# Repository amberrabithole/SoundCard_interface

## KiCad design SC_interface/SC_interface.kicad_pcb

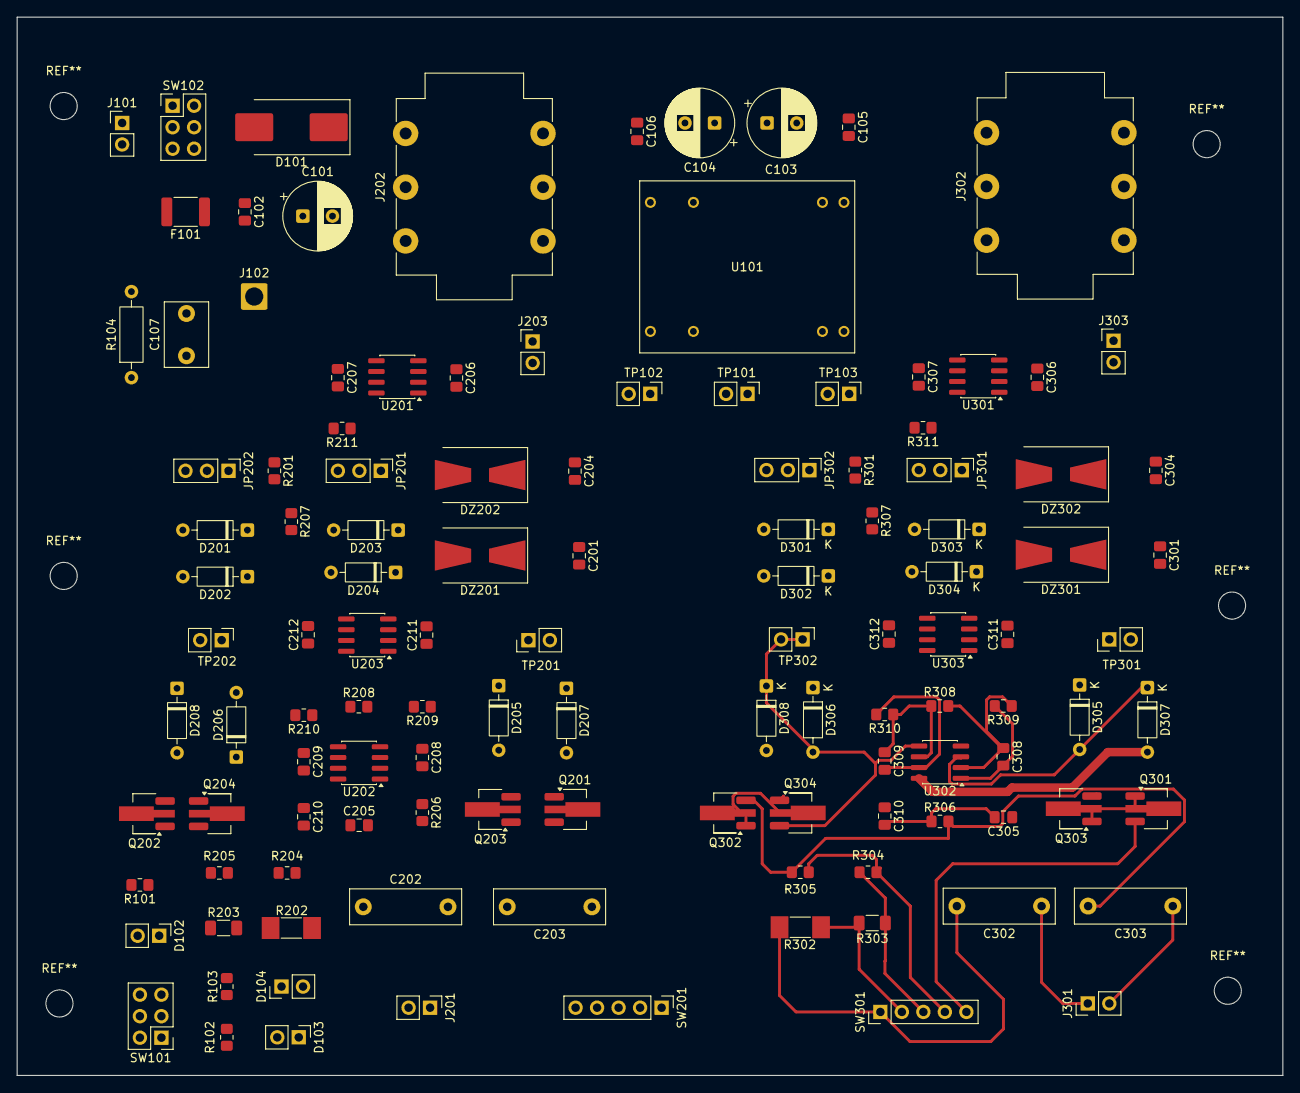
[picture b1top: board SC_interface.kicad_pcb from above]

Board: 2 copper layers, 149.5 x 125.0 mm, 120 parts (0 on the bottom side), 65 nets.

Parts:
C101, C103, C104: 330uf 25V; CP_Radial_D8.0mm_P3.50mm
C102, C105, C106, C201, C204, C205, C206, C207, C210, C211, C212, C301, C304, C305, C306, C307, C310, C311, C312: 0.1uf; C_0805_2012Metric_Pad1.18x1.45mm_HandSolder
C107: 10nF 1kV; C_Disc_D7.5mm_W5.0mm_P5.00mm
C202, C203, C302, C303: 0.47uf 400V; C_Rect_L13.0mm_W4.0mm_P10.00mm_FKS3_FKP3_MKS4
C208, C209, C308, C309: 15pF; C_0805_2012Metric_Pad1.18x1.45mm_HandSolder
D101: SMCJ6.0A; D_SMC_Handsoldering
D102: M_PWR; PinHeader_1x02_P2.54mm_Vertical
D103: PWR_PS; PinHeader_1x02_P2.54mm_Vertical
D104: PWR_NEG; PinHeader_1x02_P2.54mm_Vertical
D201, D202, D203, D204, D205, D206, D207, D208, D301, D302, D303, D304, D305, D306, D307, D308: 1N4148; D_DO-35_SOD27_P7.62mm_Horizontal
DZ201, DZ202, DZ301, DZ302: 1SMB5917; D_SMB-SMC_Universal_Handsoldering
F101: MF-MSMF110; Fuse_1812_4532Metric_Pad1.30x3.40mm_HandSolder
J101: 5V_PWR; PinHeader_1x02_P2.54mm_Vertical
J102: J_chassis; SolderWire-1.5sqmm_1x01_D1.7mm_OD3mm
J201, J301: Input; PinHeader_1x02_P2.54mm_Vertical
J202, J302: BalancedOut; Jack_6.35mm_Neutrik_NMJ6HCD2_Horizontal
J203, J303: Output_BNC; PinHeader_1x02_P2.54mm_Vertical
JP201, JP301: Clamp1; PinHeader_1x03_P2.54mm_Vertical
JP202, JP302: Clamp2; PinHeader_1x03_P2.54mm_Vertical
Q201, Q202, Q203, Q204, Q301, Q302, Q303, Q304: LND150N8; SOT-89-3_Handsoldering
R101: 470R; R_0805_2012Metric_Pad1.20x1.40mm_HandSolder
R102, R103: 3K; R_0805_2012Metric_Pad1.20x1.40mm_HandSolder
R104: 1M, 1W; R_Axial_DIN0207_L6.3mm_D2.5mm_P10.16mm_Horizontal
R201, R207, R301, R307: 1k; R_0805_2012Metric_Pad1.20x1.40mm_HandSolder
R202, R302: 90.9k; R_MELF_MMB-0207
R203, R303: 9.09k; R_1206_3216Metric_Pad1.30x1.75mm_HandSolder
R204, R304: 909; R_0805_2012Metric_Pad1.20x1.40mm_HandSolder
R205, R305: 102; R_0805_2012Metric_Pad1.20x1.40mm_HandSolder
R206, R306: 100k; R_0805_2012Metric_Pad1.20x1.40mm_HandSolder
R208, R308: 10k; R_0805_2012Metric_Pad1.20x1.40mm_HandSolder
R209, R210, R309, R310: 7.5k; R_0805_2012Metric_Pad1.20x1.40mm_HandSolder
R211, R311: 200R; R_0805_2012Metric_Pad1.20x1.40mm_HandSolder
SW101: Main Power; PinHeader_2x03_P2.54mm_Vertical
SW102: Master SW; PinHeader_2x03_P2.54mm_Vertical
SW201, SW301: SW_Select1; PinHeader_1x05_P2.54mm_Vertical
TP101: TP_POS; PinHeader_1x02_P2.54mm_Vertical
TP102: TP_NEG; PinHeader_1x02_P2.54mm_Vertical
TP103: TP_GND; PinHeader_1x02_P2.54mm_Vertical
TP201, TP301: TP_IN_HOT; PinHeader_1x02_P2.54mm_Vertical
TP202, TP302: TP_IN_COLD; PinHeader_1x02_P2.54mm_Vertical
U101: JCA0305D03; XPDCDCCONV
U201, U301: DRV135UA; SOIC-8_3.9x4.9mm_P1.27mm
U202, U302: U2 OPA1656IDR; SOIC-8_3.9x4.9mm_P1.27mm
U203, U303: INA134UA; SOIC-8_3.9x4.9mm_P1.27mm

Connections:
+VDC: C205.1, C207.1, C212.1, C305.1, C307.1, C312.1, D207.2 (A), D208.2 (A), D307.2 (A), D308.2 (A), R102.1, R201.2, R301.2, SW101.3 (C), TP101.1, TP101.2, U201.6 (V+), U202.8 (V+), U203.7 (V+), U301.6 (V+), U302.8 (V+), U303.7 (V+)
-VDC: C206.2, C210.1, C211.1, C306.2, C310.1, C311.1, D205.1 (K), D206.1 (K), D305.1 (K), D306.1 (K), R103.1, R207.1, R307.1, SW101.6 (C), TP102.1, TP102.2, U201.5 (V-), U202.4 (V-), U203.4 (V-), U301.5 (V-), U302.4 (V-), U303.4 (V-)
/5V_in: J101.1, SW102.2 (B), SW102.5 (B)
/GNDREF: C101.2, C102.2, D101.2 (A), D102.1 (K), J101.2, U101.2 (-VIN), U101.3 (-VIN2)
/Input_ChannelL/SCPROT: D201.1 (K), D203.2 (A), J203.1 (In), R211.2, U201.4 (VIN)
/Input_ChannelL/VOut_neg: J202.R, U201.1 (-VO), U201.2 (-SENSE)
/Input_ChannelL/VOut_pos: J202.T, U201.7 (+SENSE), U201.8 (+VO)
/Input_ChannelR/SCPROT: D301.1 (K), D303.2 (A), J303.1 (In), R311.2, U301.4 (VIN)
/Input_ChannelR/VOut_neg: J302.R, U301.1 (-VO), U301.2 (-SENSE)
/Input_ChannelR/VOut_pos: J302.T, U301.7 (+SENSE), U301.8 (+VO)
GND: C103.2, C104.1, C105.2, C106.2, C107.2, C201.1, C204.1, C205.2, C206.1, C207.2, C210.2, C211.2, C212.2, C301.1, C304.1, C305.2, C306.1, C307.2, C310.2, C311.2, C312.2, D103.1 (K), D104.2 (A), D202.2 (A), D204.1 (K), D302.2 (A), D304.1 (K), DZ201.2 (A), DZ202.1 (K), DZ301.2 (A), DZ302.1 (K), J202.S, J203.2 (Ext), J302.S, J303.2 (Ext), R104.2, R206.1, R306.1, TP103.1, TP103.2, U101.9 (COMMON), U101.16 (COMMON2), U201.3 (GND), U203.1 (REF), U301.3 (GND), U303.1 (REF)
unnamed: C202.2, R202.2, SW201.1
unnamed: C302.2, R302.2, SW301.1
unnamed: C101.1, C102.1, D101.1 (K), F101.2, R101.1, U101.22 (+VIN), U101.23 (+VIN2)
unnamed: D102.2 (A), R101.2
unnamed: D103.2 (A), R102.2
unnamed: D104.1 (K), R103.2
unnamed: D201.2 (A), JP201.2 (C), R201.1
unnamed: D202.1 (K), JP201.1 (A)
unnamed: D203.1 (K), JP202.2 (C), R207.2
unnamed: D204.2 (A), JP202.1 (A)
unnamed: D205.2 (A), D207.1 (K), Q203.3 (D), TP201.1, TP201.2, U202.3 (+)
unnamed: D206.2 (A), D208.1 (K), Q204.3 (D), TP202.1, TP202.2, U202.5 (+)
unnamed: D301.2 (A), JP301.2 (C), R301.1
unnamed: D302.1 (K), JP301.1 (A)
unnamed: D303.1 (K), JP302.2 (C), R307.2
unnamed: D304.2 (A), JP302.1 (A)
unnamed: D305.2 (A), D307.1 (K), Q303.3 (D), TP301.1, TP301.2, U302.3 (+)
unnamed: D306.2 (A), D308.1 (K), Q304.3 (D), TP302.1, TP302.2, U302.5 (+)
unnamed: C201.2, DZ201.1 (K), JP201.3 (B)
unnamed: C204.2, DZ202.2 (A), JP202.3 (B)
unnamed: C301.2, DZ301.1 (K), JP301.3 (B)
unnamed: C304.2, DZ302.2 (A), JP302.3 (B)
unnamed: C107.1, J102.1 (Pin_1_1), R104.1
unnamed: C203.1, J201.2 (Ext)
unnamed: C202.1, J201.1 (In)
unnamed: C303.1, J301.2 (Ext)
unnamed: C302.1, J301.1 (In)
unnamed: Q201.3 (D), SW201.5
unnamed: Q201.1 (G), Q201.2 (S), Q203.1 (G), Q203.2 (S)
unnamed: C203.2, Q202.3 (D), R205.1, R206.2
unnamed: Q202.1 (G), Q202.2 (S), Q204.1 (G), Q204.2 (S)
unnamed: Q301.3 (D), SW301.5
unnamed: Q301.1 (G), Q301.2 (S), Q303.1 (G), Q303.2 (S)
unnamed: C303.2, Q302.3 (D), R305.1, R306.2
unnamed: Q302.1 (G), Q302.2 (S), Q304.1 (G), Q304.2 (S)
unnamed: R202.1, R203.2, SW201.2
unnamed: R203.1, R204.2, SW201.3
unnamed: R204.1, R205.2, SW201.4
unnamed: R302.1, R303.2, SW301.2
unnamed: R303.1, R304.2, SW301.3
unnamed: R304.1, R305.2, SW301.4
unnamed: C103.1, C105.1, SW101.2 (B), U101.14 (+VOUT)
unnamed: C104.2, C106.1, SW101.5 (B), U101.11 (-VOUT)
unnamed: F101.1, SW102.3 (C), SW102.6 (C)
unnamed: C208.1, R208.2, R209.1, U202.2 (-)
unnamed: C209.1, R208.1, R210.1, U202.6 (-)
unnamed: C208.2, R209.2, U202.1, U203.3 (IN+)
unnamed: C209.2, R210.2, U202.7, U203.2 (IN-)
unnamed: R211.1, U203.5 (SENSE), U203.6 (OUT)
unnamed: C308.1, R308.2, R309.1, U302.2 (-)
unnamed: C309.1, R308.1, R310.1, U302.6 (-)
unnamed: C308.2, R309.2, U302.1, U303.3 (IN+)
unnamed: C309.2, R310.2, U302.7, U303.2 (IN-)
unnamed: R311.1, U303.5 (SENSE), U303.6 (OUT)
